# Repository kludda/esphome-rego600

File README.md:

# esphome-rego600

External component for ESPHome enabling communication with Rego 6xx heat pump controllers.

&#x2615; [Buy me a coffee :)](https://paypal.me/davidalind)

## Overview
This project started as a fork of https://github.com/dala318/esphome-rego600 but that version had issues with blocking UART calls, causing WDT resets during setup when adding all registers. **This fork is a major rewrite using a non-blocking state machine.**

Huge shout-out to ["How to connect heat pump with Rego 6xx controller"](https://rago600.sourceforge.net/) who I guess did most of the reverse-engineering of the protocol used by most Rego600 interfaces out there.

To my knowledge, this is now a working component that performs as intended.

> **NOTE**: I'm a mechanical design engineer, not an electronics or software engineer—so expect the quality to reflect that. :)

## Hardware
The component is not bound to any specific hardware setup; it only requires that a UART port of the MCU be connected to the external communication port of the heat pump.

I used an ESP-C3 Super Mini development board with an external antenna ([this one](https://www.aliexpress.com/item/1005008047249439.html)). The ESP is mounted on the DB-9 connector, and the antenna is mounted outside the heat pump enclosure. For the UART interface, I use a logic-level converter for the Rego RX signal and a simple voltage divider for the Rego TX signal. Note that the Rego TX signal is inverted.

You can find manufacturing files adopted for ["JLC PCB"](https://jlcpcb.com/) (jlcpcb-*), and a KiCad 9.0 project, in the  [`/hardware`](/hardware) folder. The connector and ESP32 Super Mini board are marked as DNP (Do Not Populate).

> **WARNING**: I don’t know whether the Rego UART is isolated, so I can’t recommend this setup — I’m only describing what I have done.

> **INFO**: Do not use long cables for the serial bus. The checksum is calculated only for the data portion of the packet, so transmission errors in the command section won’t be detected. Data for read is "0". If a read command is corrupted, the Rego may interpret it as a write command and write 0 to that register. (I’ve got the T-shirt.)

## Configuration in ESPHome

See [rego600.yaml](rego600.yaml) for an example ESPHome configuration. It includes all registers known to me and some ideas for automation.

> **NOTE**: The label in my heat pump says *Rego637E*. However, the registers listed as "Rego600-635" on (https://rago600.sourceforge.net/) are what work for me. Those are also used in [rego600.yaml](rego600.yaml)

## Licensing
This work is licensed under the **CC-BY 4.0 International License**. To view a copy of this license, visit: https://creativecommons.org/licenses/by/4.0/

Parts of the code dealing with composing and decomposing UART commands most likely originate from the Arduino sketch provided by [how to connect heat pump with Rego 6xx controller](https://rago600.sourceforge.net/), which is licensed as *postcardware* (see link for details).

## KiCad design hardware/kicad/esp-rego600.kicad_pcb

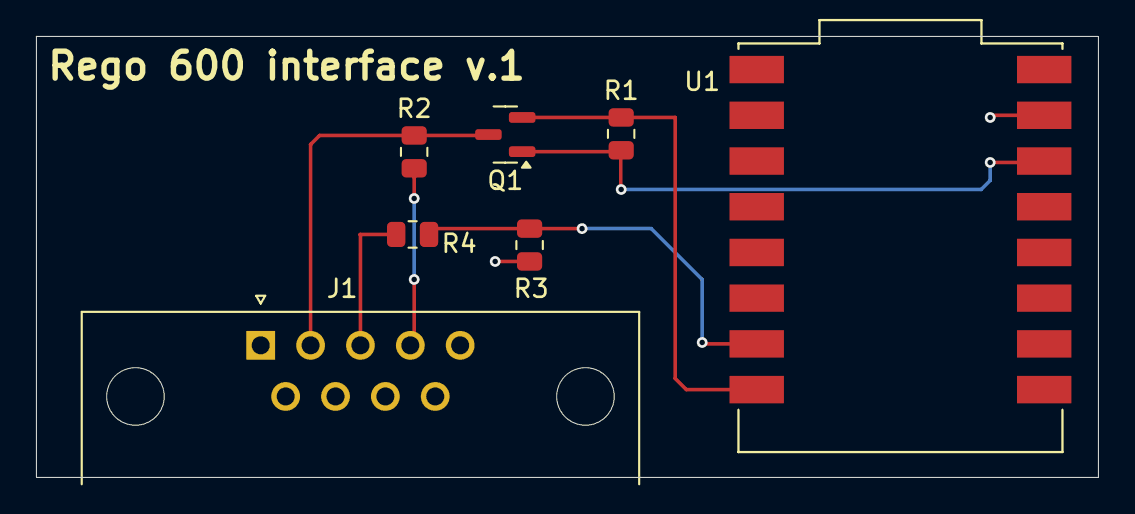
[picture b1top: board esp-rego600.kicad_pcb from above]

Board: 2 copper layers, 59.0 x 24.5 mm, 7 parts (0 on the bottom side), 7 nets.

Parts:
J1: DE9_Pins; DSUB-9_Pins_Horizontal_P2.77x2.84mm_EdgePinOffset4.94mm_Hou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
Q1: BSS138; SOT-23
R1, R2, R4: 10K 5%; R_0805_2012Metric
R3: 20K 5%; R_0805_2012Metric
U1: ESP32-C3_SUPERMINI_SMD; MODULE_ESP32-C3_SUPERMINI

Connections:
3.3V: Q1.1 (G), R1.1, U1.3.3 (3V3)
5V: J1.4, R2.1
/HV1: Q1.3 (D), R2.2
/LV1: Q1.2 (S), R1.2, U1.21 (GPIO21)
GND: J1.5, R3.2, U1.G (GND)
unnamed: J1.3, R4.2
unnamed: R3.1, R4.1, U1.20 (GPIO20)

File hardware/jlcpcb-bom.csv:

"Comment","Designator","Footprint","LCSC"
"BSS138","Q1","Package_TO_SOT_SMD:SOT-23","C78284"
"20K 5%","R3","Resistor_SMD:R_0805_2012Metric","C4328"
"10K 5%","R1,R2,R4","Resistor_SMD:R_0805_2012Metric","C17414"

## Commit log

2025-04-10 Minor fixes
2025-10-08 Complete rewrite to state-machine
    Add command to be able to read and write to multiple register types
    Update README.md
    readme
    Update rego_number.cpp
    Update rego600.yaml
    handle command request in other state than idle
2025-11-05 Add photos
2025-11-05 Added KiCad project and JLCPCB manufacturing files.
2025-11-05 Spelling + grammar
